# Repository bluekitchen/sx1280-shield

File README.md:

# SX1280 Breakout Board in Arduino Form-Factor

This is a breakout board for the SX1280 in Arduino form-factor to use with e.g. STM32 Nucleo Dev Boards or similar. It uses the [E28-2G4M12S module from EBYTE](https://www.ebyte.com/en/new-view-info.aspx?id=297), which is readily available from AliExpress or Banggod. 

## Motivation

The official SX1280 shield (SX1280RF1ZHP) from the Semtech's [SX1280DVK1ZHP](https://www.semtech.com/products/wireless-rf/24-ghz-transceivers/sx1280dvk1zhp) or [SX1280ED1ZHP](https://www.semtech.com/products/wireless-rf/lora-transceivers/sx1280ed1zhp) development kits have resistors in the SPI lines, which limit the SPI speed to about 5 Mhz. 

While SPI speed is not relevant for LoRa operations, implementing Bluetooth Low Energy requires to transfer data packets to/from the SX1280 quickly, which is easier to achieve with the max SPI speed of 18 Mhz. This breakout board was created to avoid replacing the resistors with 0 Ohm ones on the official shield and to allow the full 18 Mhz SPI speed.

## Usage

Signal | Arduino | Debug connector
-------|---------|----------------
3V3    |  3V3    | 
GND    |  GND    |   1
NSS    |  D7     |   2
SCK    |  SCK    |   3
MOSI   |  MOSI   |   4
MISO   |  MISO   |   5
BUSY   |  D3     |   6
DIO1   |  D5     |   7
DIO2   |         |   8
DIO3   |         |   9
nReset |  A0     |  10

All signals are provided at the J1 debug connector to hook up a logic analyzer.

The SX1280 can map various IRQ requests on the DIO1-3 pins. DIO1 is pre-assigned in this shield, while the DIO2 and DIO3 can be connected via jumper J2 to other GPIO pins if needed. 

Please note: The SX1280 is not 5V tolerant.

## References
- [SX1280 Product Page](https://www.semtech.com/products/wireless-rf/24-ghz-transceivers/sx1280)
- [SX1280 Datahsheet](https://semtech.my.salesforce.com/sfc/p/E0000000JelG/a/2R000000HoCW/8EVYKPLcthcKCB_cKzApAc6Xf6tAHtn9.UKcOh7SNmg)
- [28-2G4M12S Datasheet](https://www.ebyte.com/en/downpdf.aspx?id=286)

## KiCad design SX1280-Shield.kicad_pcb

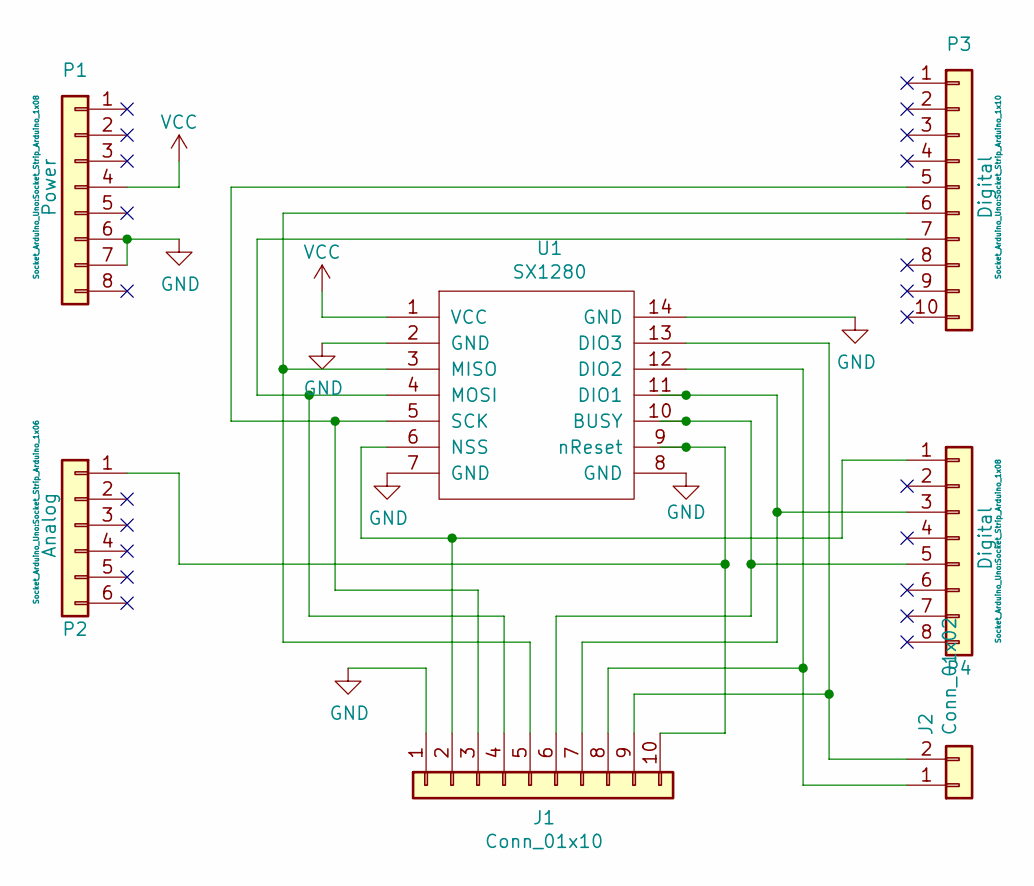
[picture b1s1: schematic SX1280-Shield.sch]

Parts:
J1: Conn_01x10; Socket_Strip_Arduino_1x10
J2: Conn_01x02; PinHeader_1x02_P2.54mm_Vertical
P1: Power; Socket_Strip_Arduino_1x08
P2: Analog; Socket_Strip_Arduino_1x06
P3: Digital; Socket_Strip_Arduino_1x10
P4: Digital; Socket_Strip_Arduino_1x08
U1: SX1280; E28-2G4M12S-SX1280

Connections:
GND: J1.1, P1.6, P1.7, U1.2 (GND), U1.7 (GND), U1.8 (GND), U1.14 (GND)
unnamed: J1.2, P4.1, U1.6 (NSS)
unnamed: J1.3, P3.5, U1.5 (SCK)
unnamed: J1.4, P3.7, U1.4 (MOSI)
unnamed: J1.5, P3.6, U1.3 (MISO)
unnamed: J1.6, P4.5, U1.10 (BUSY)
unnamed: J1.7, P4.3, U1.11 (DIO1)
unnamed: J1.8, J2.1, U1.12 (DIO2)
unnamed: J1.9, J2.2, U1.13 (DIO3)
unnamed: J1.10, P2.1, U1.9 (nReset)
VCC: P1.4, U1.1 (VCC)

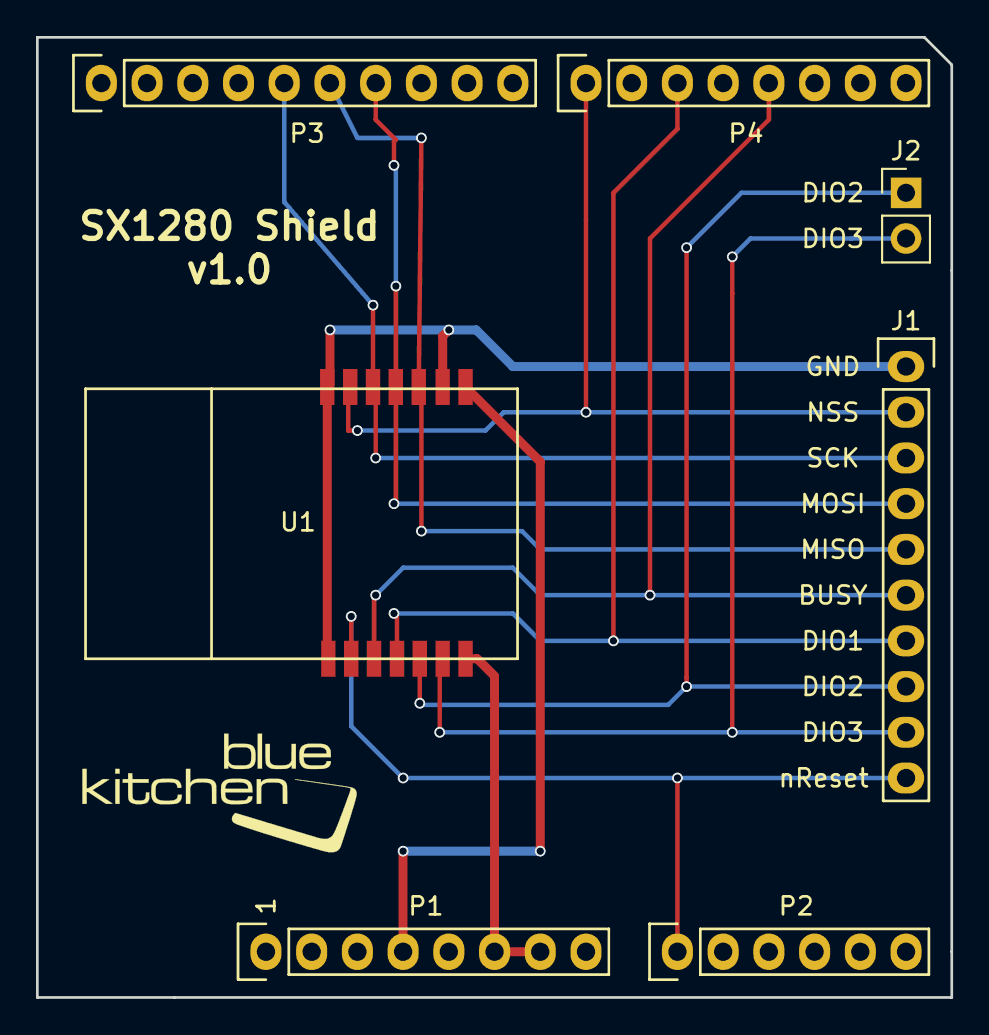
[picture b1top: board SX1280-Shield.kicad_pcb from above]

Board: 2 copper layers, 50.8 x 53.3 mm, 7 parts (0 on the bottom side), 11 nets.

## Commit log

2021-03-11 add documentation
